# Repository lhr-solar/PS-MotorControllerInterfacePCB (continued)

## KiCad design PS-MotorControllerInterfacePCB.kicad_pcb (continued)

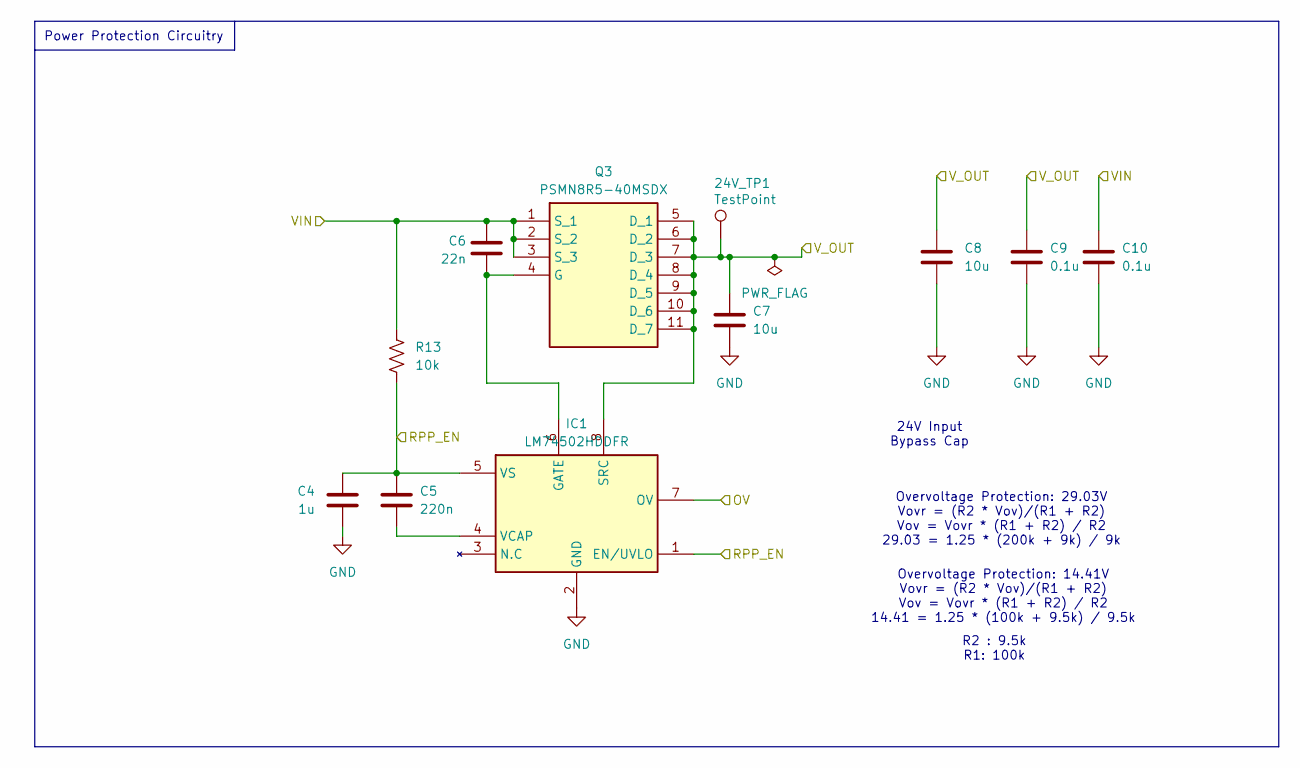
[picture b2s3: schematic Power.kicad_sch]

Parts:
24V_TP1: TestPoint; TestPoint_Pad_1.0x1.0mm
C4: 1u; C_0603_1608Metric_Pad1.08x0.95mm_HandSolder; Manufacturer_Part_Number MLASU168SB5105KTNA01
C5: 220n; C_0603_1608Metric_Pad1.08x0.95mm_HandSolder; Manufacturer_Part_Number MSASU168SB7224KTNB25
C6: 22n; C_0603_1608Metric_Pad1.08x0.95mm_HandSolder; Manufacturer_Part_Number 06035C223K4T4A
C7, C8: 10u; C_0805_2012Metric_Pad1.18x1.45mm_HandSolder; Manufacturer_Part_Number GRM21BR61H106KE43K
C9, C10: 0.1u; C_0603_1608Metric_Pad1.08x0.95mm_HandSolder; Manufacturer_Part_Number MLASH168SB7104KTNA01
IC1: LM74502HDDFR; SOT65P280X110-8N; Mouser Part Number 595-LM74502HDDFR
Q3: PSMN8R5-40MSDX; Mouser Part Number 771-PSMN8R5-40MSDX
R13: 10k; R_0603_1608Metric_Pad0.98x0.95mm_HandSolder; Manufacturer_Part_Number CRCW060310K0FKEI

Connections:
+12V: 24V_TP1.1, C7.1, C8.1, C9.1, IC1.8 (SRC), Q3.5 (D_1), Q3.6 (D_2), Q3.7 (D_3), Q3.8 (D_4), Q3.9 (D_5), Q3.10 (D_6), Q3.11 (D_7); also elsewhere on the board
/12V_BUS: C6.2, C10.1, Q3.1 (S_1), Q3.2 (S_2), Q3.3 (S_3), R13.1; also elsewhere on the board
/Power12V/OV: IC1.7 (OV); also elsewhere on the board
/RPP_EN12: C4.2, C5.1, IC1.1 (EN/UVLO), IC1.5 (VS), R13.2; also elsewhere on the board
GND: C4.1, C7.2, C8.2, C9.2, C10.2, IC1.2 (GND); also elsewhere on the board
unnamed: C6.1, IC1.6 (GATE), Q3.4 (G)
unnamed: C5.2, IC1.4 (VCAP)

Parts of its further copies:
24V_TP3: TestPoint; TestPoint_Pad_1.0x1.0mm
C11: 1u; C_0603_1608Metric_Pad1.08x0.95mm_HandSolder; Manufacturer_Part_Number MLASU168SB5105KTNA01
C12: 220n; C_0603_1608Metric_Pad1.08x0.95mm_HandSolder; Manufacturer_Part_Number MSASU168SB7224KTNB25
C13: 22n; C_0603_1608Metric_Pad1.08x0.95mm_HandSolder; Manufacturer_Part_Number 06035C223K4T4A
C14, C15: 10u; C_0805_2012Metric_Pad1.18x1.45mm_HandSolder; Manufacturer_Part_Number GRM21BR61H106KE43K
C20, C21: 0.1u; C_0603_1608Metric_Pad1.08x0.95mm_HandSolder; Manufacturer_Part_Number MLASH168SB7104KTNA01
IC2: LM74502HDDFR; SOT65P280X110-8N; Mouser Part Number 595-LM74502HDDFR
Q4: PSMN8R5-40MSDX; Mouser Part Number 771-PSMN8R5-40MSDX
R14: 10k; R_0603_1608Metric_Pad0.98x0.95mm_HandSolder; Manufacturer_Part_Number CRCW060310K0FKEI

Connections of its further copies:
+24V: 24V_TP3.1, C14.1, C15.1, C20.1, IC2.8 (SRC), Q4.5 (D_1), Q4.6 (D_2), Q4.7 (D_3), Q4.8 (D_4), Q4.9 (D_5), Q4.10 (D_6), Q4.11 (D_7); also elsewhere on the board
/Power24V/OV: IC2.7 (OV); also elsewhere on the board
/RPP_EN24: C11.2, C12.1, IC2.1 (EN/UVLO), IC2.5 (VS), R14.2; also elsewhere on the board
/VIN_24V: C13.2, C21.1, Q4.1 (S_1), Q4.2 (S_2), Q4.3 (S_3), R14.1; also elsewhere on the board
GND: C11.1, C14.2, C15.2, C20.2, C21.2, IC2.2 (GND); also elsewhere on the board
unnamed: C13.1, IC2.6 (GATE), Q4.4 (G)
unnamed: C12.2, IC2.4 (VCAP)

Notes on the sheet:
Overvoltage Protection: 29.03V Vovr = (R2 * Vov)/(R1 + R2) Vov = Vovr * (R1 + R2) / R2 29.03 = 1.25 * (200k + 9k) / 9k
Overvoltage Protection: 14.41V Vovr = (R2 * Vov)/(R1 + R2) Vov = Vovr * (R1 + R2) / R2 14.41 = 1.25 * (100k + 9.5k) / 9.5k
Power Protection Circuitry
R2 : 9.5k R1: 100k
24V Input Bypass Cap

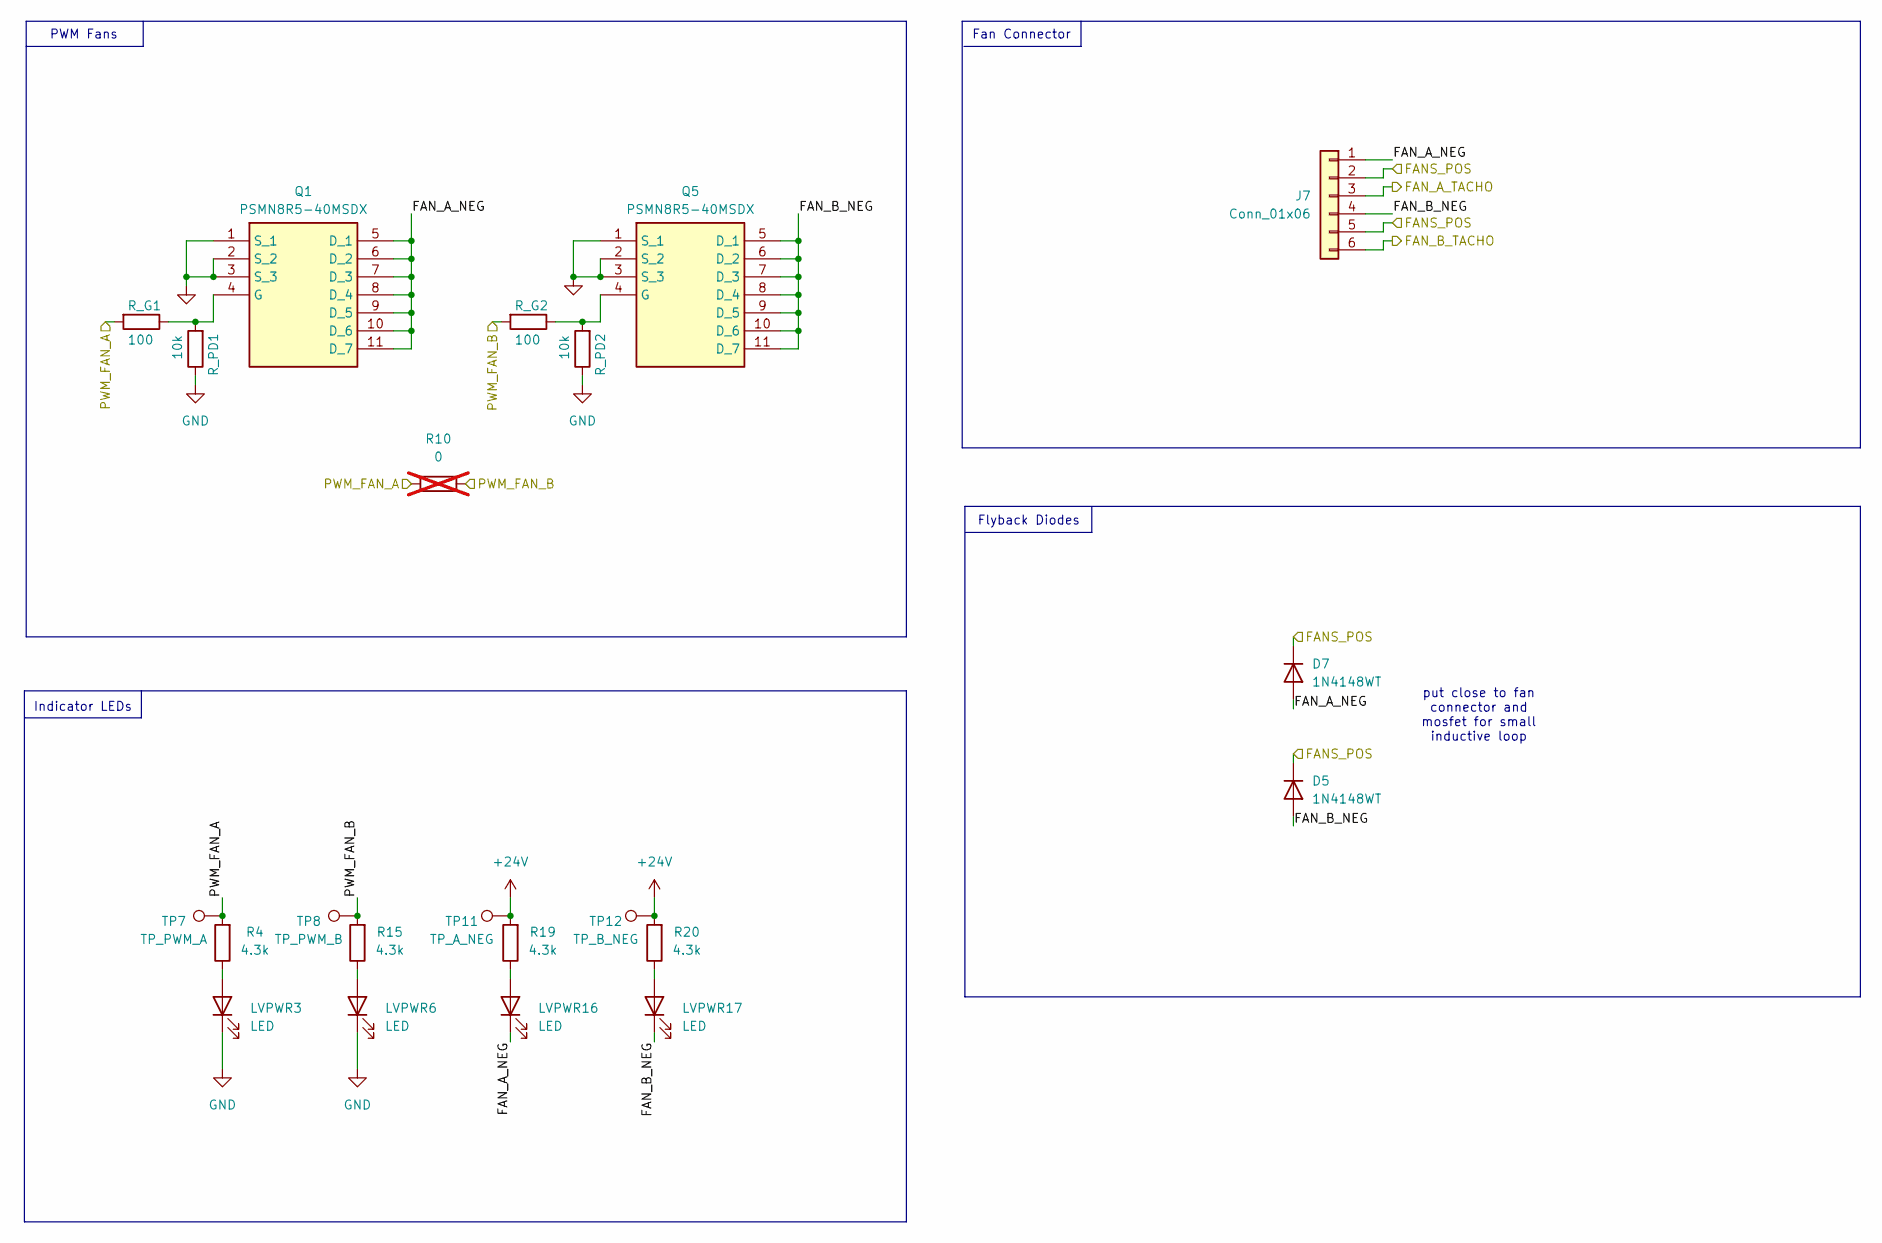
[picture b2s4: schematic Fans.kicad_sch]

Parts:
D5, D7: 1N4148WT; D_SOD-523; Manufacturer_Part_Number NCD0603R1
J7: Conn_01x06; Molex_Nano-Fit_105309-xx06_1x06_P2.50mm_Vertical
LVPWR3, LVPWR6, LVPWR16, LVPWR17: LED; LED_0603_1608Metric
Q1, Q5: PSMN8R5-40MSDX; Mouser Part Number 771-PSMN8R5-40MSDX
R4, R15, R19, R20: 4.3k; R_0603_1608Metric_Pad0.98x0.95mm_HandSolder; Manufacturer_Part_Number CRCW06034K30FKEA
R10: 0; R_0603_1608Metric_Pad0.98x0.95mm_HandSolder; Manufacturer_Part_Number CRCW06030000Z0EE; not fitted
R_G1, R_G2: 100; R_0603_1608Metric_Pad0.98x0.95mm_HandSolder; Manufacturer_Part_Number CRCW0603120RFKEC
R_PD1, R_PD2: 10k; R_0603_1608Metric_Pad0.98x0.95mm_HandSolder; Manufacturer_Part_Number CRCW060310K0FKEI
TP7: TP_PWM_A; TestPoint_Pad_1.0x1.0mm
TP8: TP_PWM_B; TestPoint_Pad_1.0x1.0mm
TP11: TP_A_NEG; TestPoint_Pad_1.0x1.0mm
TP12: TP_B_NEG; TestPoint_Pad_1.0x1.0mm

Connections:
+24V: D5.1 (K), D7.1 (K), J7.2, J7.5, R19.2, R20.2, TP11.1, TP12.1; also elsewhere on the board
/FAN_A_TACHO: J7.3; also elsewhere on the board
/FAN_B_TACHO: J7.6; also elsewhere on the board
/Fans/FAN_A_NEG: D7.2 (A), J7.1, LVPWR16.1 (K), Q1.5 (D_1), Q1.6 (D_2), Q1.7 (D_3), Q1.8 (D_4), Q1.9 (D_5), Q1.10 (D_6), Q1.11 (D_7)
/Fans/FAN_B_NEG: D5.2 (A), J7.4, LVPWR17.1 (K), Q5.5 (D_1), Q5.6 (D_2), Q5.7 (D_3), Q5.8 (D_4), Q5.9 (D_5), Q5.10 (D_6), Q5.11 (D_7)
/PWM_FAN_A: R4.2, R10.1, R_G1.2, TP7.1; also elsewhere on the board
/PWM_FAN_B: R10.2, R15.2, R_G2.2, TP8.1; also elsewhere on the board
GND: LVPWR3.1 (K), LVPWR6.1 (K), Q1.1 (S_1), Q1.2 (S_2), Q1.3 (S_3), Q5.1 (S_1), Q5.2 (S_2), Q5.3 (S_3), R_PD1.1, R_PD2.1; also elsewhere on the board
unnamed: LVPWR3.2 (A), R4.1
unnamed: LVPWR6.2 (A), R15.1
unnamed: LVPWR16.2 (A), R19.1
unnamed: LVPWR17.2 (A), R20.1
unnamed: Q1.4 (G), R_G1.1, R_PD1.2
unnamed: Q5.4 (G), R_G2.1, R_PD2.2

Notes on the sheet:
Fan Connector
Indicator LEDs
Flyback Diodes
PWM Fans
put close to fan connector and mosfet for small inductive loop

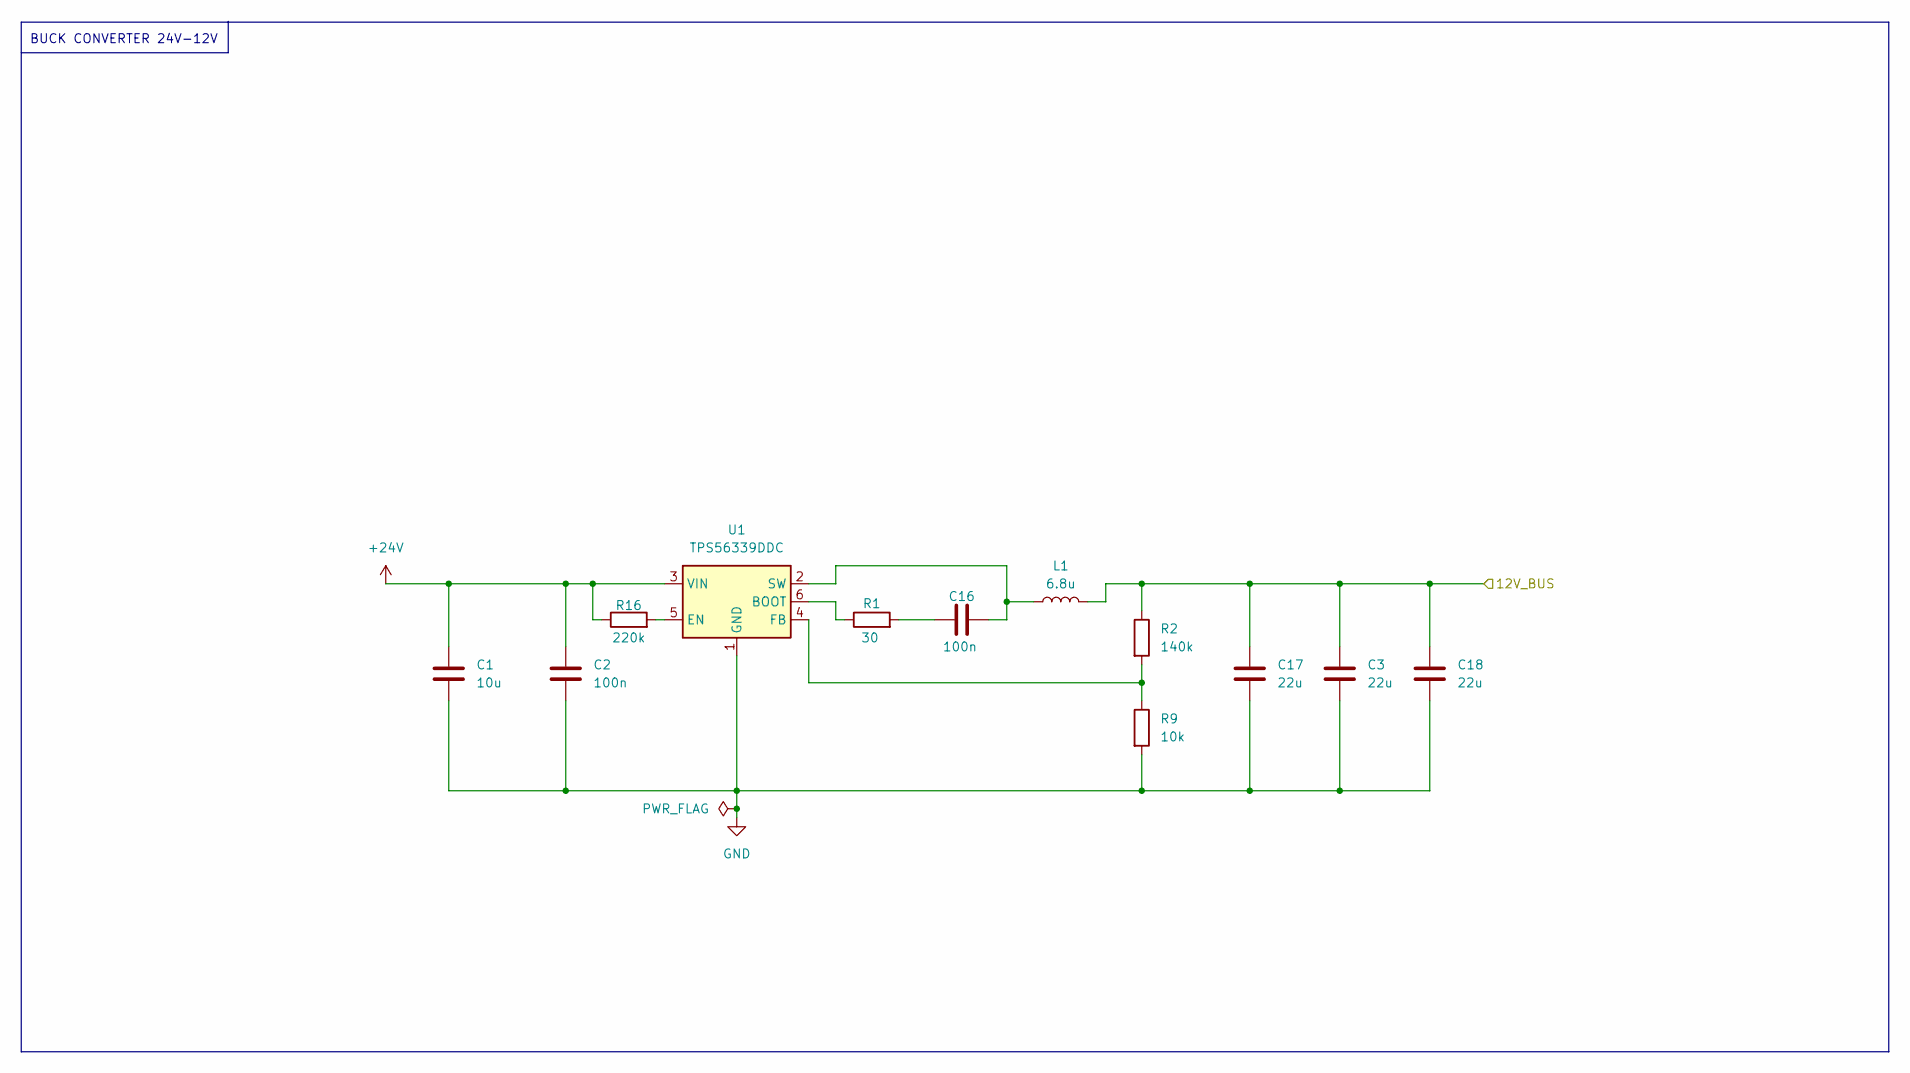
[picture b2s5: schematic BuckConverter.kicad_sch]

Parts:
C1: 10u; C_0805_2012Metric_Pad1.18x1.45mm_HandSolder; Manufacturer_Part_Number GRM21BR61H106KE43K
C2, C16: 100n; C_0603_1608Metric_Pad1.08x0.95mm_HandSolder; Manufacturer_Part_Number MLASH168SB7104KTNA01
C3, C17, C18: 22u; C_0805_2012Metric_Pad1.18x1.45mm_HandSolder
L1: 6.8u; L_6.3x6.3_H3
R1: 30; R_0603_1608Metric_Pad0.98x0.95mm_HandSolder
R2: 140k; R_0603_1608Metric_Pad0.98x0.95mm_HandSolder
R9: 10k; R_0603_1608Metric_Pad0.98x0.95mm_HandSolder; Manufacturer_Part_Number CRCW060310K0FKEI
R16: 220k; R_0603_1608Metric_Pad0.98x0.95mm_HandSolder
U1: TPS56339DDC; SOT-23-6

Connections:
+24V: C1.1, C2.1, R16.1, U1.3 (VIN); also elsewhere on the board
/12V_BUS: C3.1, C17.1, C18.1, L1.2, R2.1; also elsewhere on the board
GND: C1.2, C2.2, C3.2, C17.2, C18.2, R9.2, U1.1 (GND); also elsewhere on the board
unnamed: C16.1, R1.2
unnamed: R1.1, U1.6 (BOOT)
unnamed: R16.2, U1.5 (EN)
unnamed: R2.2, R9.1, U1.4 (FB)
unnamed: C16.2, L1.1, U1.2 (SW)

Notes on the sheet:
BUCK CONVERTER 24V-12V

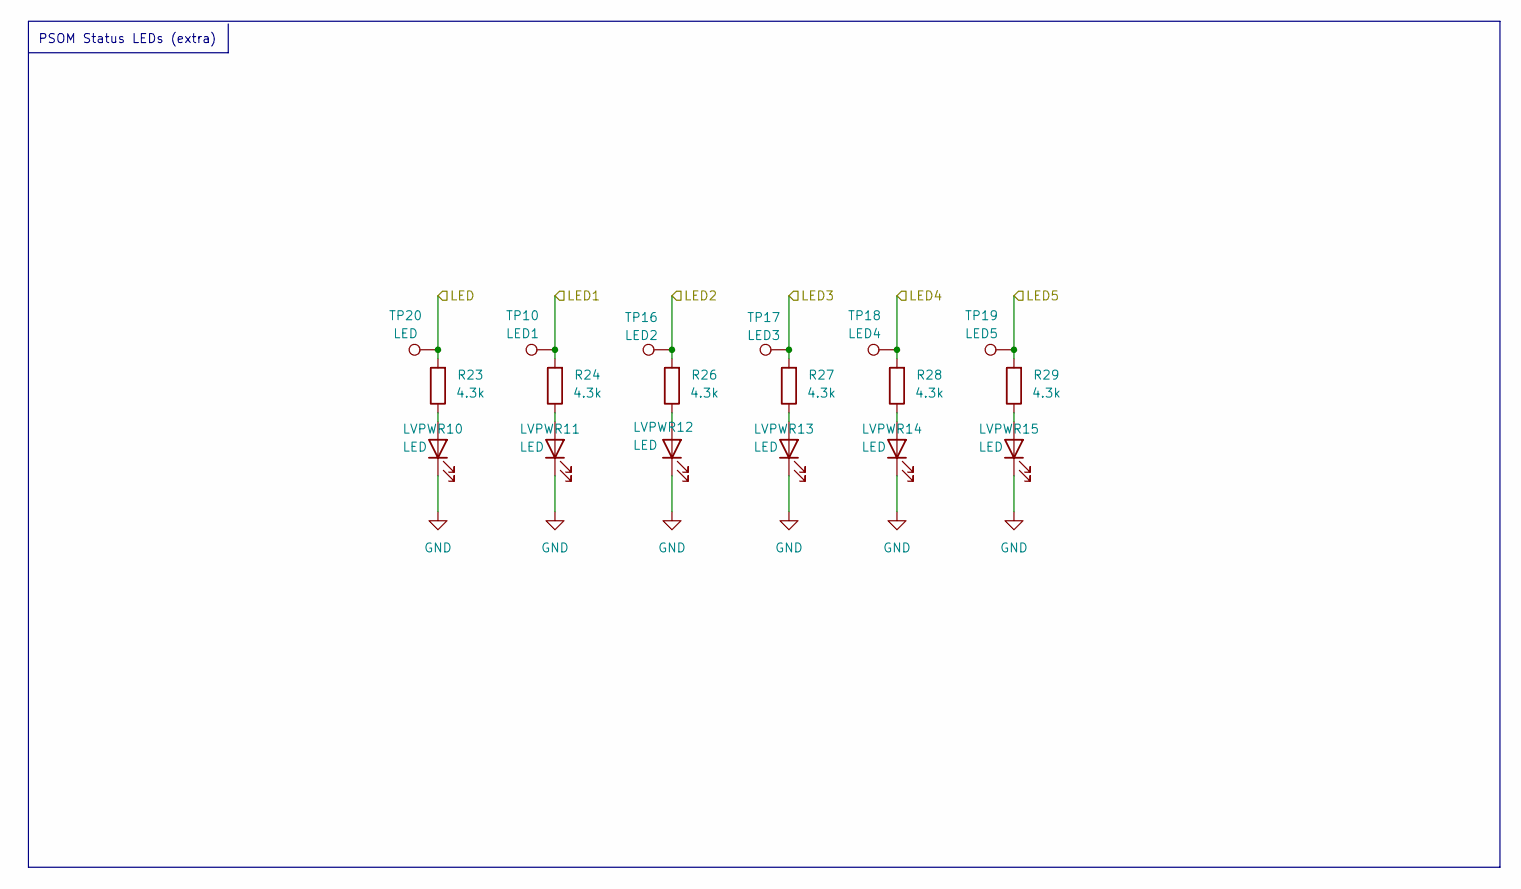
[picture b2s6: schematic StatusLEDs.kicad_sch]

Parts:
LVPWR10, LVPWR11, LVPWR12, LVPWR13, LVPWR14, LVPWR15: LED; LED_0603_1608Metric
R23, R24, R26, R27, R28, R29: 4.3k; R_0603_1608Metric_Pad0.98x0.95mm_HandSolder; Manufacturer_Part_Number CRCW06034K30FKEA
TP10: LED1; TestPoint_Pad_1.0x1.0mm
TP16: LED2; TestPoint_Pad_1.0x1.0mm
TP17: LED3; TestPoint_Pad_1.0x1.0mm
TP18: LED4; TestPoint_Pad_1.0x1.0mm
TP19: LED5; TestPoint_Pad_1.0x1.0mm
TP20: LED; TestPoint_Pad_1.0x1.0mm

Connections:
/LED: R23.2, TP20.1; also elsewhere on the board
/LED1: R24.2, TP10.1; also elsewhere on the board
/LED2: R26.2, TP16.1; also elsewhere on the board
/LED3: R27.2, TP17.1; also elsewhere on the board
/LED4: R28.2, TP18.1; also elsewhere on the board
/LED5: R29.2, TP19.1; also elsewhere on the board
GND: LVPWR10.1 (K), LVPWR11.1 (K), LVPWR12.1 (K), LVPWR13.1 (K), LVPWR14.1 (K), LVPWR15.1 (K); also elsewhere on the board
unnamed: LVPWR10.2 (A), R23.1
unnamed: LVPWR11.2 (A), R24.1
unnamed: LVPWR12.2 (A), R26.1
unnamed: LVPWR13.2 (A), R27.1
unnamed: LVPWR14.2 (A), R28.1
unnamed: LVPWR15.2 (A), R29.1

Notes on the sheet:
PSOM Status LEDs (extra)

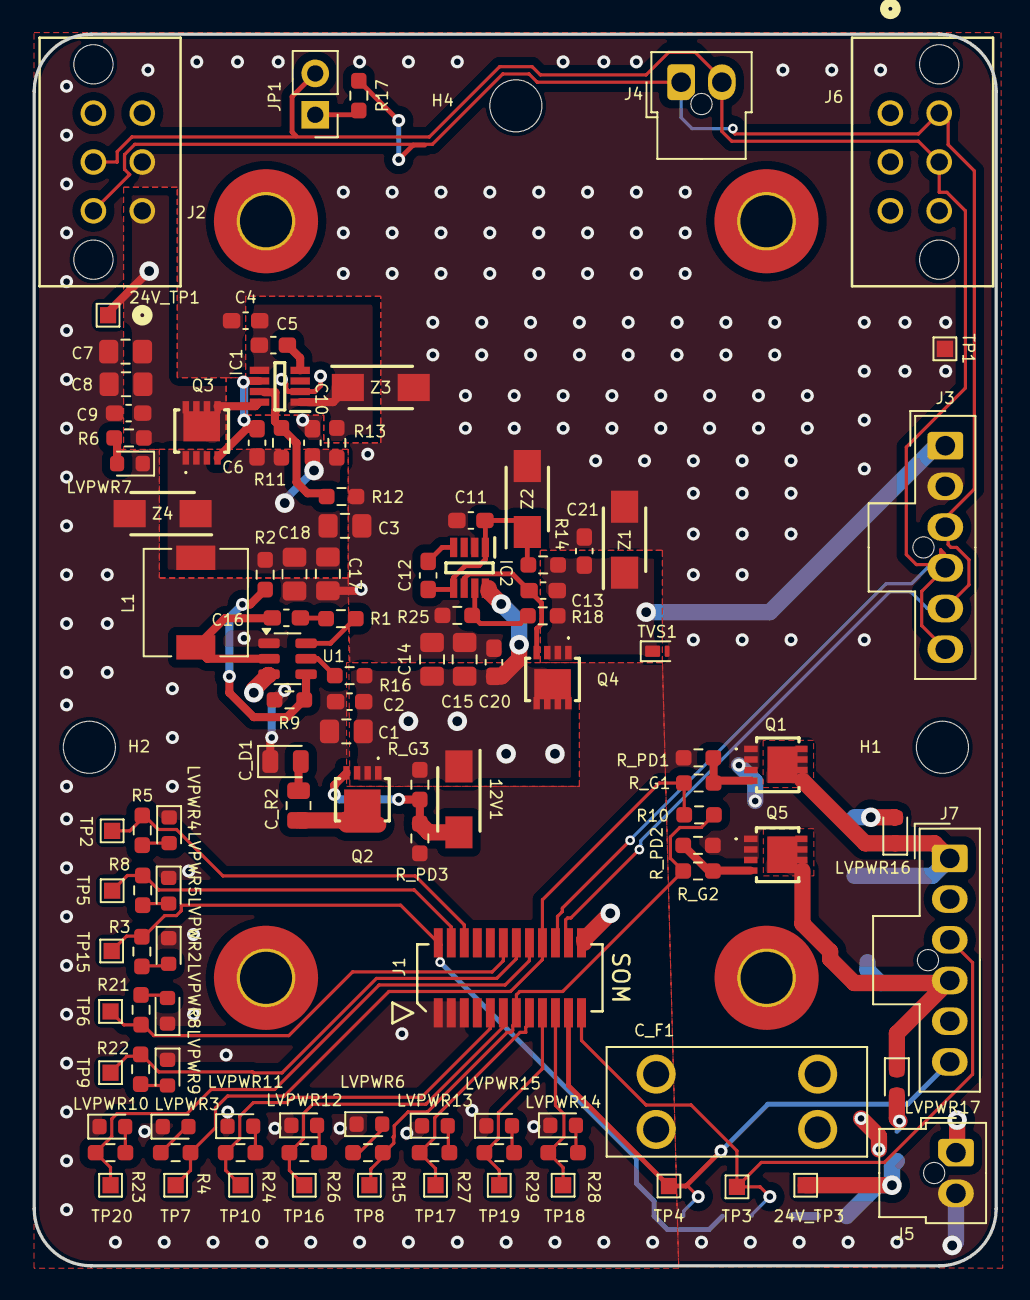
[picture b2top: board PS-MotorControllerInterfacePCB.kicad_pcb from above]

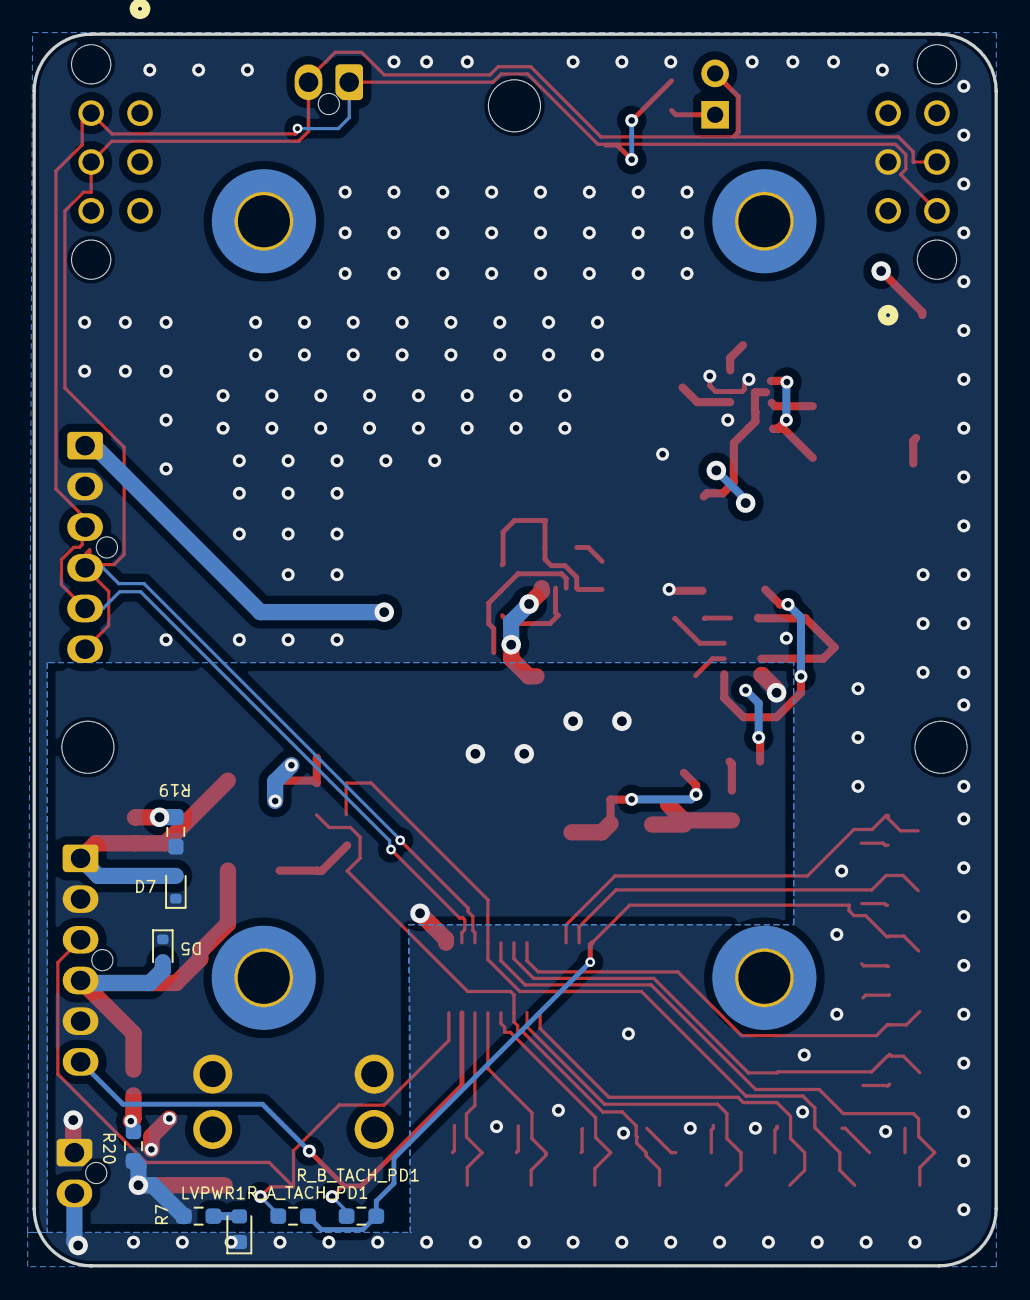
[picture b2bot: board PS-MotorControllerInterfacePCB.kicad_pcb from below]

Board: 2 copper layers, 59.1 x 75.7 mm, 124 parts (8 on the bottom side), 60 nets.

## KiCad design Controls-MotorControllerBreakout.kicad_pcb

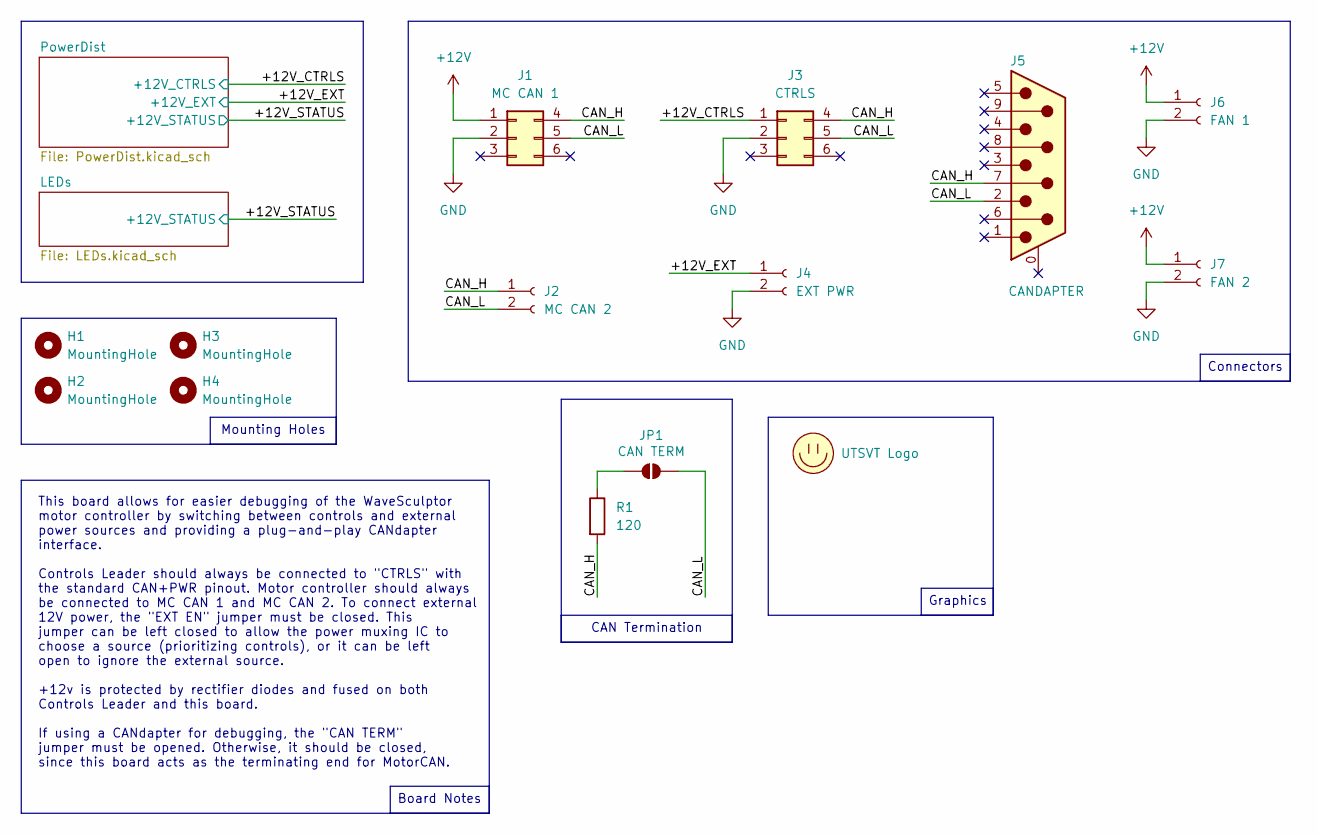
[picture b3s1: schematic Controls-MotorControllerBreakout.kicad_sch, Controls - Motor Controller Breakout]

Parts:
H1, H2, H3, H4: MountingHole; MountingHole_3mm
J1: MC CAN 1; Molex_Micro-Fit_3.0_43045-0612_2x03_P3.00mm_Vertical
J2: MC CAN 2; Molex_Micro-Fit_3.0_43650-0215_1x02_P3.00mm_Vertical
J3: CTRLS; Molex_Micro-Fit_3.0_43045-0612_2x03_P3.00mm_Vertical
J4: EXT PWR; Molex_Micro-Fit_3.0_43650-0215_1x02_P3.00mm_Vertical
J5: CANDAPTER; AMPHENOL_L77SDE09SA4CH3R
J6: FAN 1; Molex_Micro-Fit_3.0_43650-0215_1x02_P3.00mm_Vertical
J7: FAN 2; Molex_Micro-Fit_3.0_43650-0215_1x02_P3.00mm_Vertical
JP1: CAN TERM; SolderJumper-2_P1.3mm_Open_RoundedPad1.0x1.5mm
LOGO1: UTSVT Logo; UTSVT_Logo_Symbol
R1: 120; R_0805_2012Metric

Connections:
+12V: J1.1, J6.1, J7.1; also elsewhere on the board
/+12V_CTRLS: J3.1; also elsewhere on the board
/+12V_EXT: J4.1; also elsewhere on the board
/CAN_H: J1.4, J2.1, J3.4, J5.7, R1.2
/CAN_L: J1.5, J2.2, J3.5, J5.2, JP1.2 (B)
GND: J1.2, J3.2, J4.2, J6.2, J7.2; also elsewhere on the board
unnamed: JP1.1 (A), R1.1

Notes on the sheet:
This board allows for easier debugging of the WaveSculptor motor controller by switching between controls and external power sources and providing a plug-and-play CANdapter interface. Controls Leader should always be connected to "CTRLS" with the standard CAN+PWR pinout. Motor controller should alw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
Graphics
Board Notes
Mounting Holes
Connectors
CAN Termination

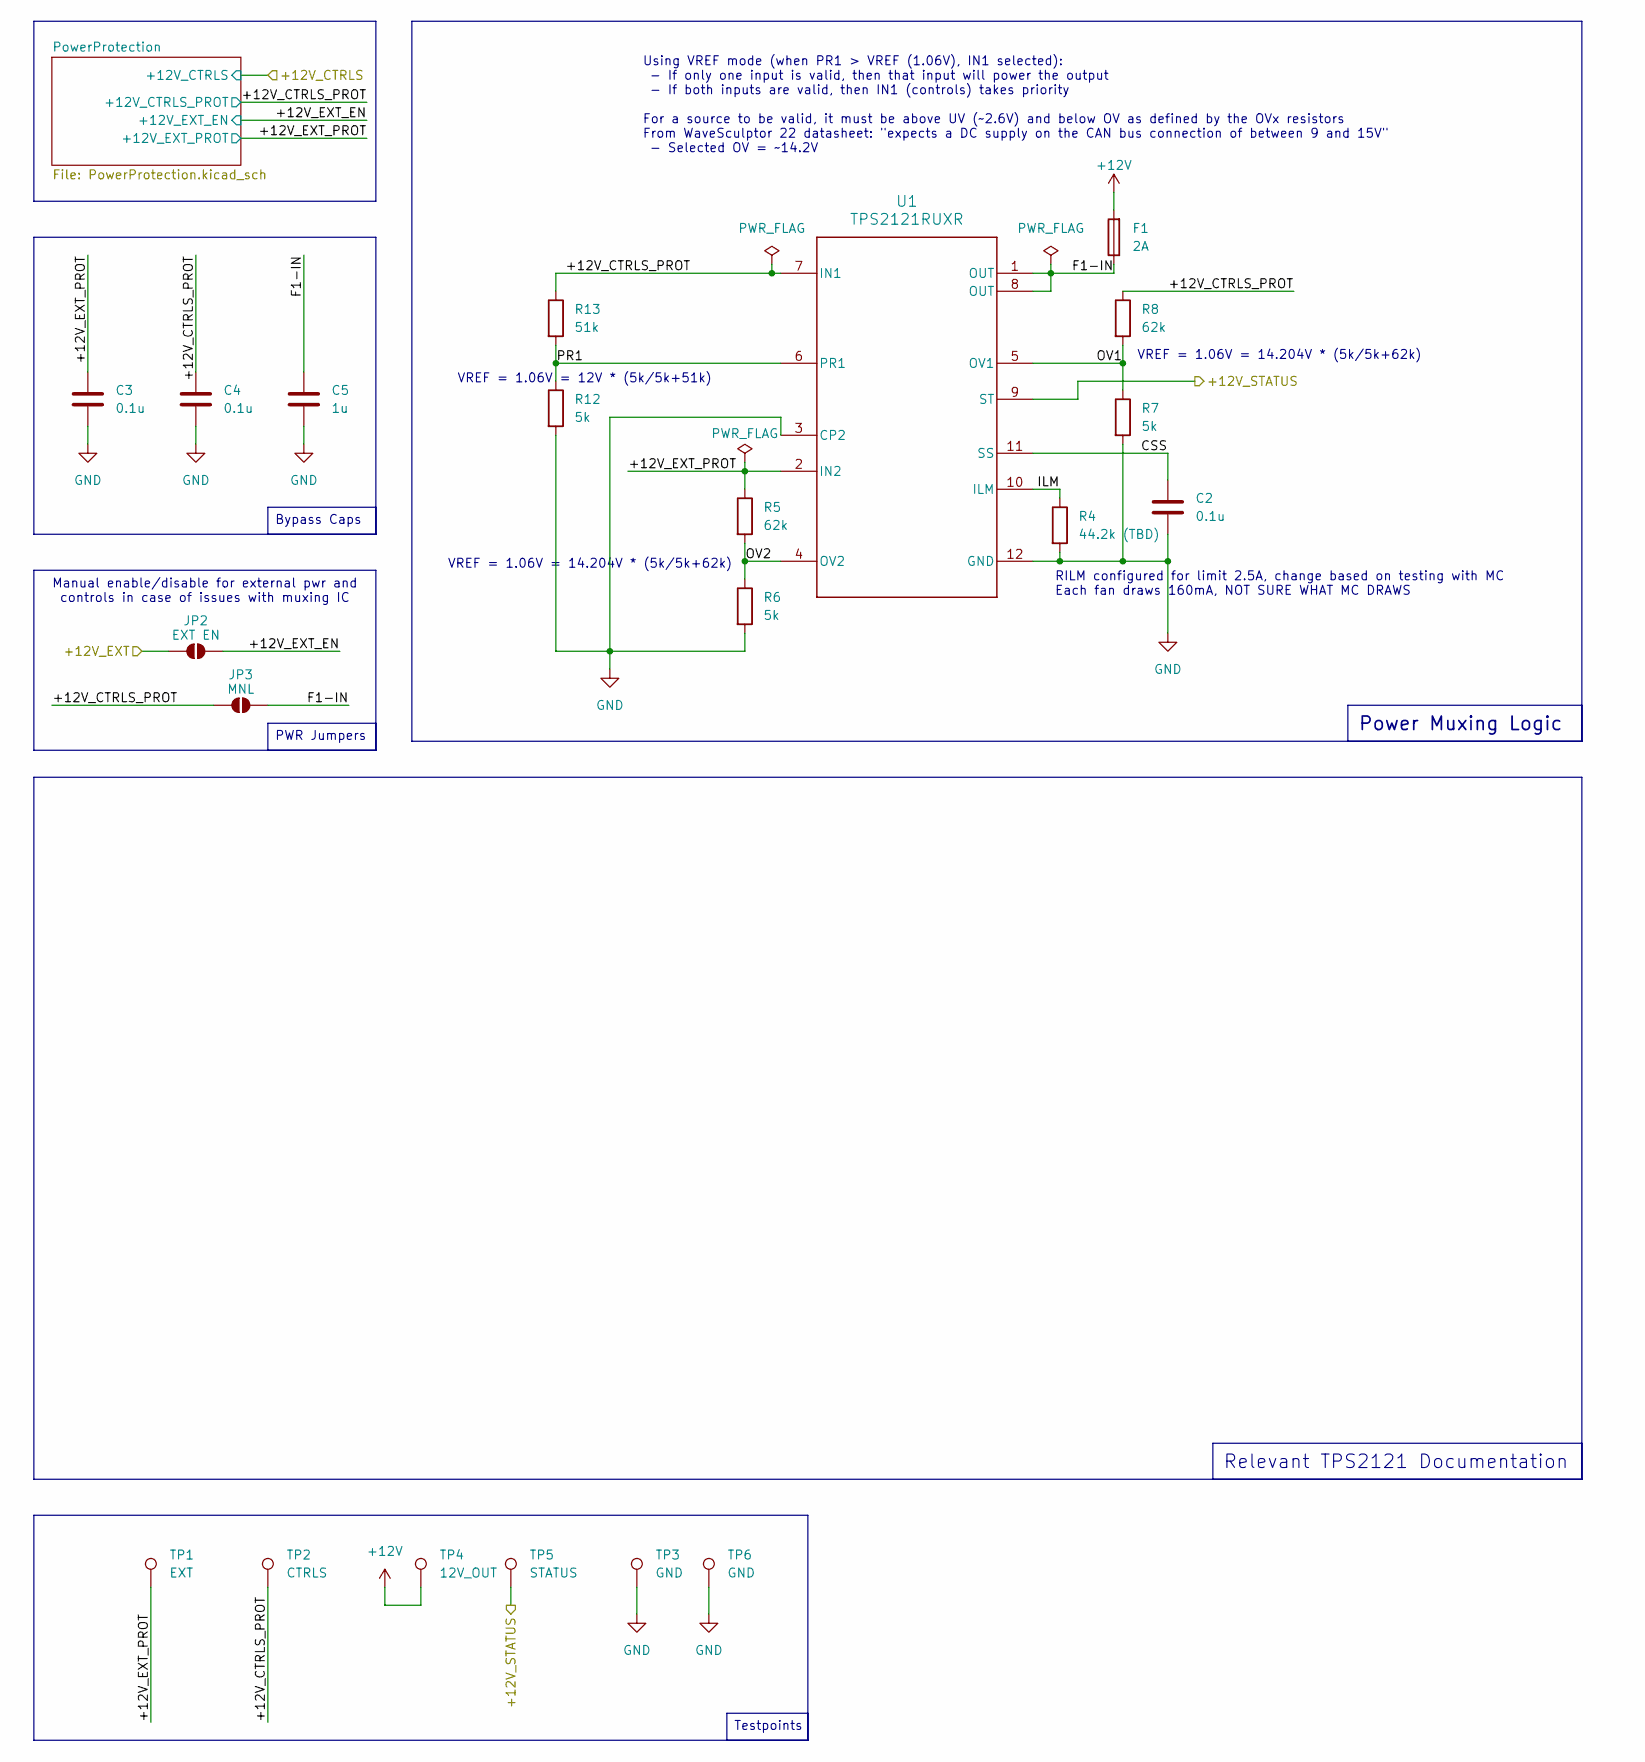
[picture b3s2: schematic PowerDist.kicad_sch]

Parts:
C2, C3, C4: 0.1u; C_0805_2012Metric
C5: 1u; C_0805_2012Metric
F1: 2A; Fuse_1206_3216Metric; Mouser Part Number 576-0440002.WR
JP2: EXT EN; SolderJumper-2_P1.3mm_Open_RoundedPad1.0x1.5mm
JP3: MNL; SolderJumper-2_P1.3mm_Open_RoundedPad1.0x1.5mm
R4: 44.2k (TBD); R_0805_2012Metric
R5, R8: 62k; R_0805_2012Metric
R6, R7, R12: 5k; R_0805_2012Metric
R13: 51k; R_0805_2012Metric
TP1: EXT; TestPoint_Pad_1.0x1.0mm
TP2: CTRLS; TestPoint_Pad_1.0x1.0mm
TP3, TP6: GND; TestPoint_Pad_1.0x1.0mm
TP4: 12V_OUT; TestPoint_Pad_1.0x1.0mm
TP5: STATUS; TestPoint_Pad_1.0x1.0mm
U1: TPS2121RUXR; RUX0012A

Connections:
+12V: F1.2, TP4.1; also elsewhere on the board
/+12V_EXT: JP2.1 (A); also elsewhere on the board
/+12V_STATUS: TP5.1, U1.9 (ST); also elsewhere on the board
/PowerDist/+12V_CTRLS_PROT: C4.1, JP3.1 (A), R8.1, R13.1, TP2.1, U1.7 (IN1); also elsewhere on the board
/PowerDist/+12V_EXT_EN: JP2.2 (B); also elsewhere on the board
/PowerDist/+12V_EXT_PROT: C3.1, R5.1, TP1.1, U1.2 (IN2); also elsewhere on the board
/PowerDist/CSS: C2.1, U1.11 (SS)
/PowerDist/F1-IN: C5.1, F1.1, JP3.2 (B), U1.1 (OUT), U1.8 (OUT)
/PowerDist/ILM: R4.1, U1.10 (ILM)
/PowerDist/OV1: R7.1, R8.2, U1.5 (OV1)
/PowerDist/OV2: R5.2, R6.1, U1.4 (OV2)
/PowerDist/PR1: R12.1, R13.2, U1.6 (PR1)
GND: C2.2, C3.2, C4.2, C5.2, R4.2, R6.2, R7.2, R12.2, TP3.1, TP6.1, U1.3 (CP2), U1.12 (GND); also elsewhere on the board

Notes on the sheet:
VREF = 1.06V = 14.204V * (5k/5k+62k)
VREF = 1.06V = 12V * (5k/5k+51k)
Using VREF mode (when PR1 > VREF (1.06V), IN1 selected): - If only one input is valid, then that input will power the output - If both inputs are valid, then IN1 (controls) takes priority For a source to be valid, it must be above UV (~2.6V) and below OV as defined by the OVx resistors From WaveScu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
RILM configured for limit 2.5A, change based on testing with MC Each fan draws 160mA, NOT SURE WHAT MC DRAWS
Manual enable/disable for external pwr and controls in case of issues with muxing IC
Testpoints
Relevant TPS2121 Documentation
PWR Jumpers
Bypass Caps
Power Muxing Logic

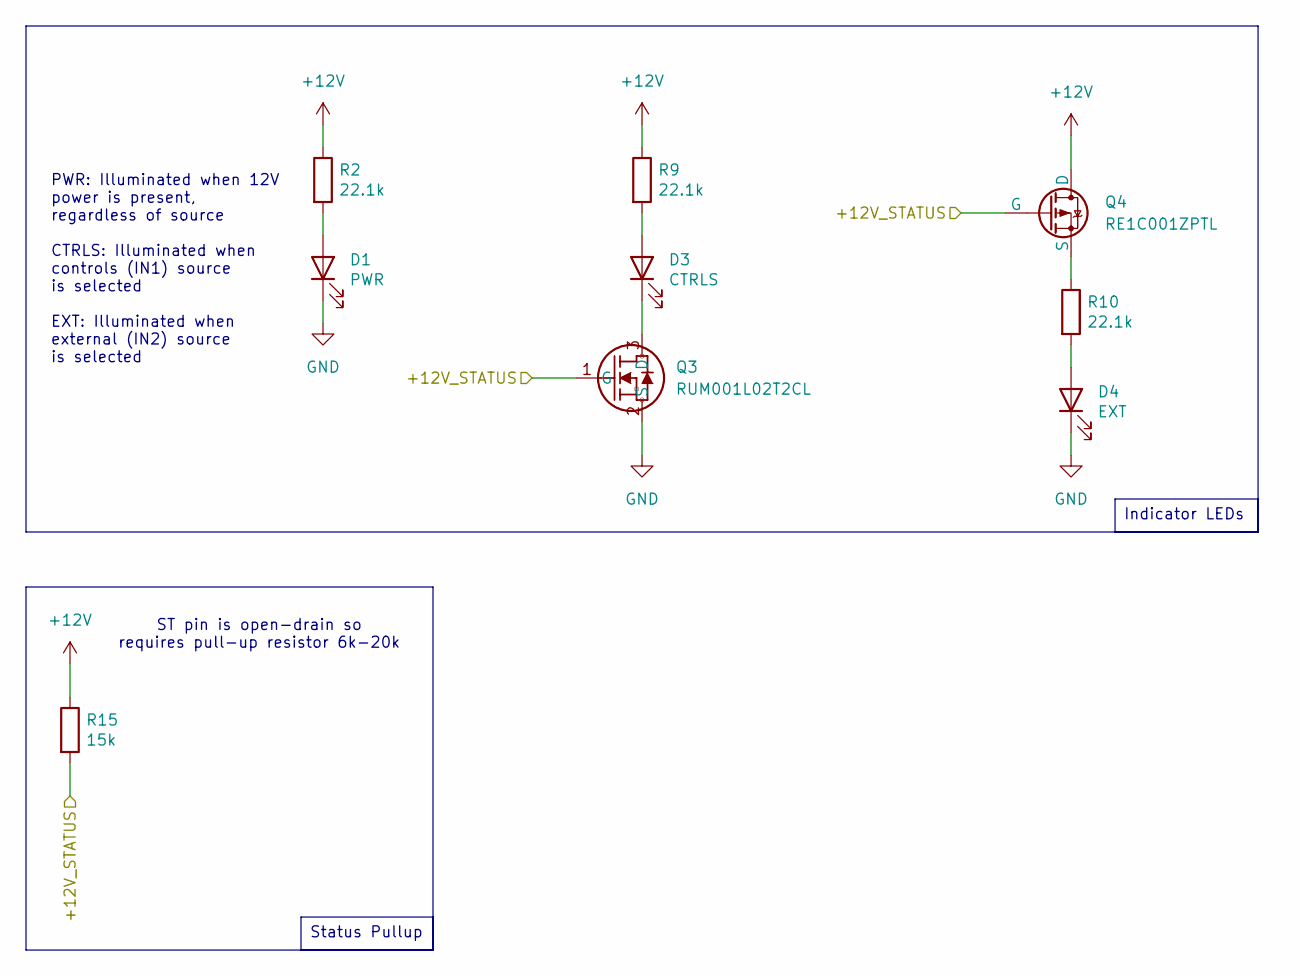
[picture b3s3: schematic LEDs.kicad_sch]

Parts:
D1: PWR; LED_0805_2012Metric; Mouser Part Number 604-APTD2012LCGCK
D3: CTRLS; LED_0805_2012Metric; Mouser Part Number 604-APTD2012LCGCK
D4: EXT; LED_0805_2012Metric; Mouser Part Number 604-APTD2012LCGCK
Q3: RUM001L02T2CL; TRANS_RUM001_ROM
Q4: RE1C001ZPTL; TRANS_RE1C001_ROM
R2, R9, R10: 22.1k; R_0805_2012Metric; Mouser Part Number 71-CRCW0805-22.1K-E3
R15: 15k; R_0805_2012Metric; Mouser Part Number 71-CRCW0805-22.1K-E3

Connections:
+12V: Q4.1 (D), R2.1, R9.1, R15.1; also elsewhere on the board
/+12V_STATUS: Q3.1 (G), Q4.2 (G), R15.2; also elsewhere on the board
GND: D1.1 (K), D4.1 (K), Q3.2 (S); also elsewhere on the board
unnamed: D1.2 (A), R2.2
unnamed: D3.2 (A), R9.2
unnamed: D3.1 (K), Q3.3 (D)
unnamed: D4.2 (A), R10.2
unnamed: Q4.3 (S), R10.1

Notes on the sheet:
ST pin is open-drain so requires pull-up resistor 6k-20k
PWR: Illuminated when 12V power is present, regardless of source CTRLS: Illuminated when controls (IN1) source is selected EXT: Illuminated when external (IN2) source is selected
Indicator LEDs
Status Pullup

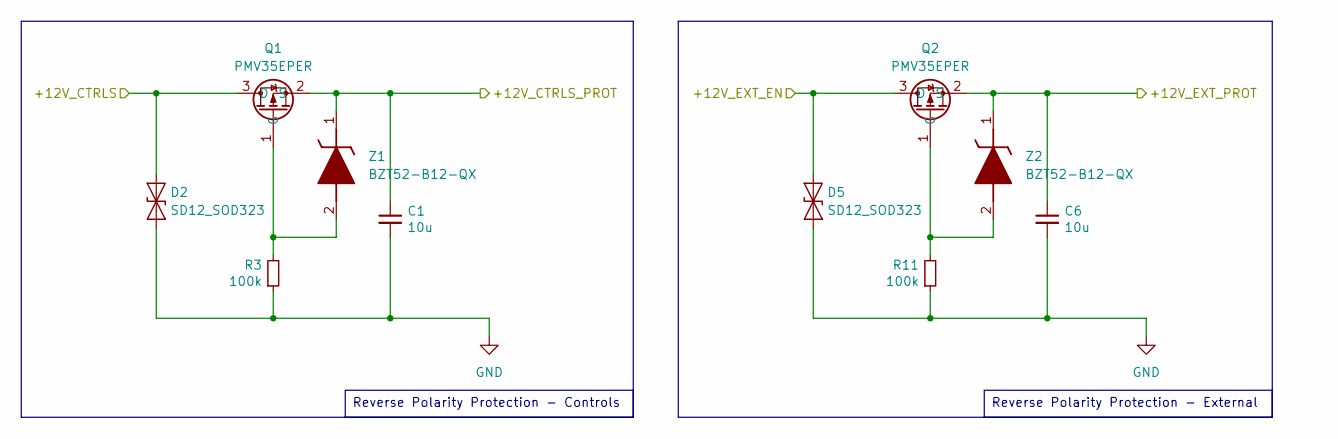
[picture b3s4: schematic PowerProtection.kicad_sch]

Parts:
C1, C6: 10u; C_0805_2012Metric
D2, D5: SD12_SOD323; D_SOD-323
Q1, Q2: PMV35EPER; SOT-23
R3, R11: 100k; R_0805_2012Metric
Z1, Z2: BZT52-B12-QX; BZT52B12QX; Mouser Part Number 771-BZT52-B12-QX

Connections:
/+12V_CTRLS: D2.2 (A2), Q1.3 (D); also elsewhere on the board
/PowerDist/+12V_CTRLS_PROT: C1.1, Q1.2 (S), Z1.1 (K); also elsewhere on the board
/PowerDist/+12V_EXT_EN: D5.2 (A2), Q2.3 (D); also elsewhere on the board
/PowerDist/+12V_EXT_PROT: C6.1, Q2.2 (S), Z2.1 (K); also elsewhere on the board
GND: C1.2, C6.2, D2.1 (A1), D5.1 (A1), R3.1, R11.1; also elsewhere on the board
unnamed: Q1.1 (G), R3.2, Z1.2 (A)
unnamed: Q2.1 (G), R11.2, Z2.2 (A)

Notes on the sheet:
Reverse Polarity Protection - External
Reverse Polarity Protection - Controls
